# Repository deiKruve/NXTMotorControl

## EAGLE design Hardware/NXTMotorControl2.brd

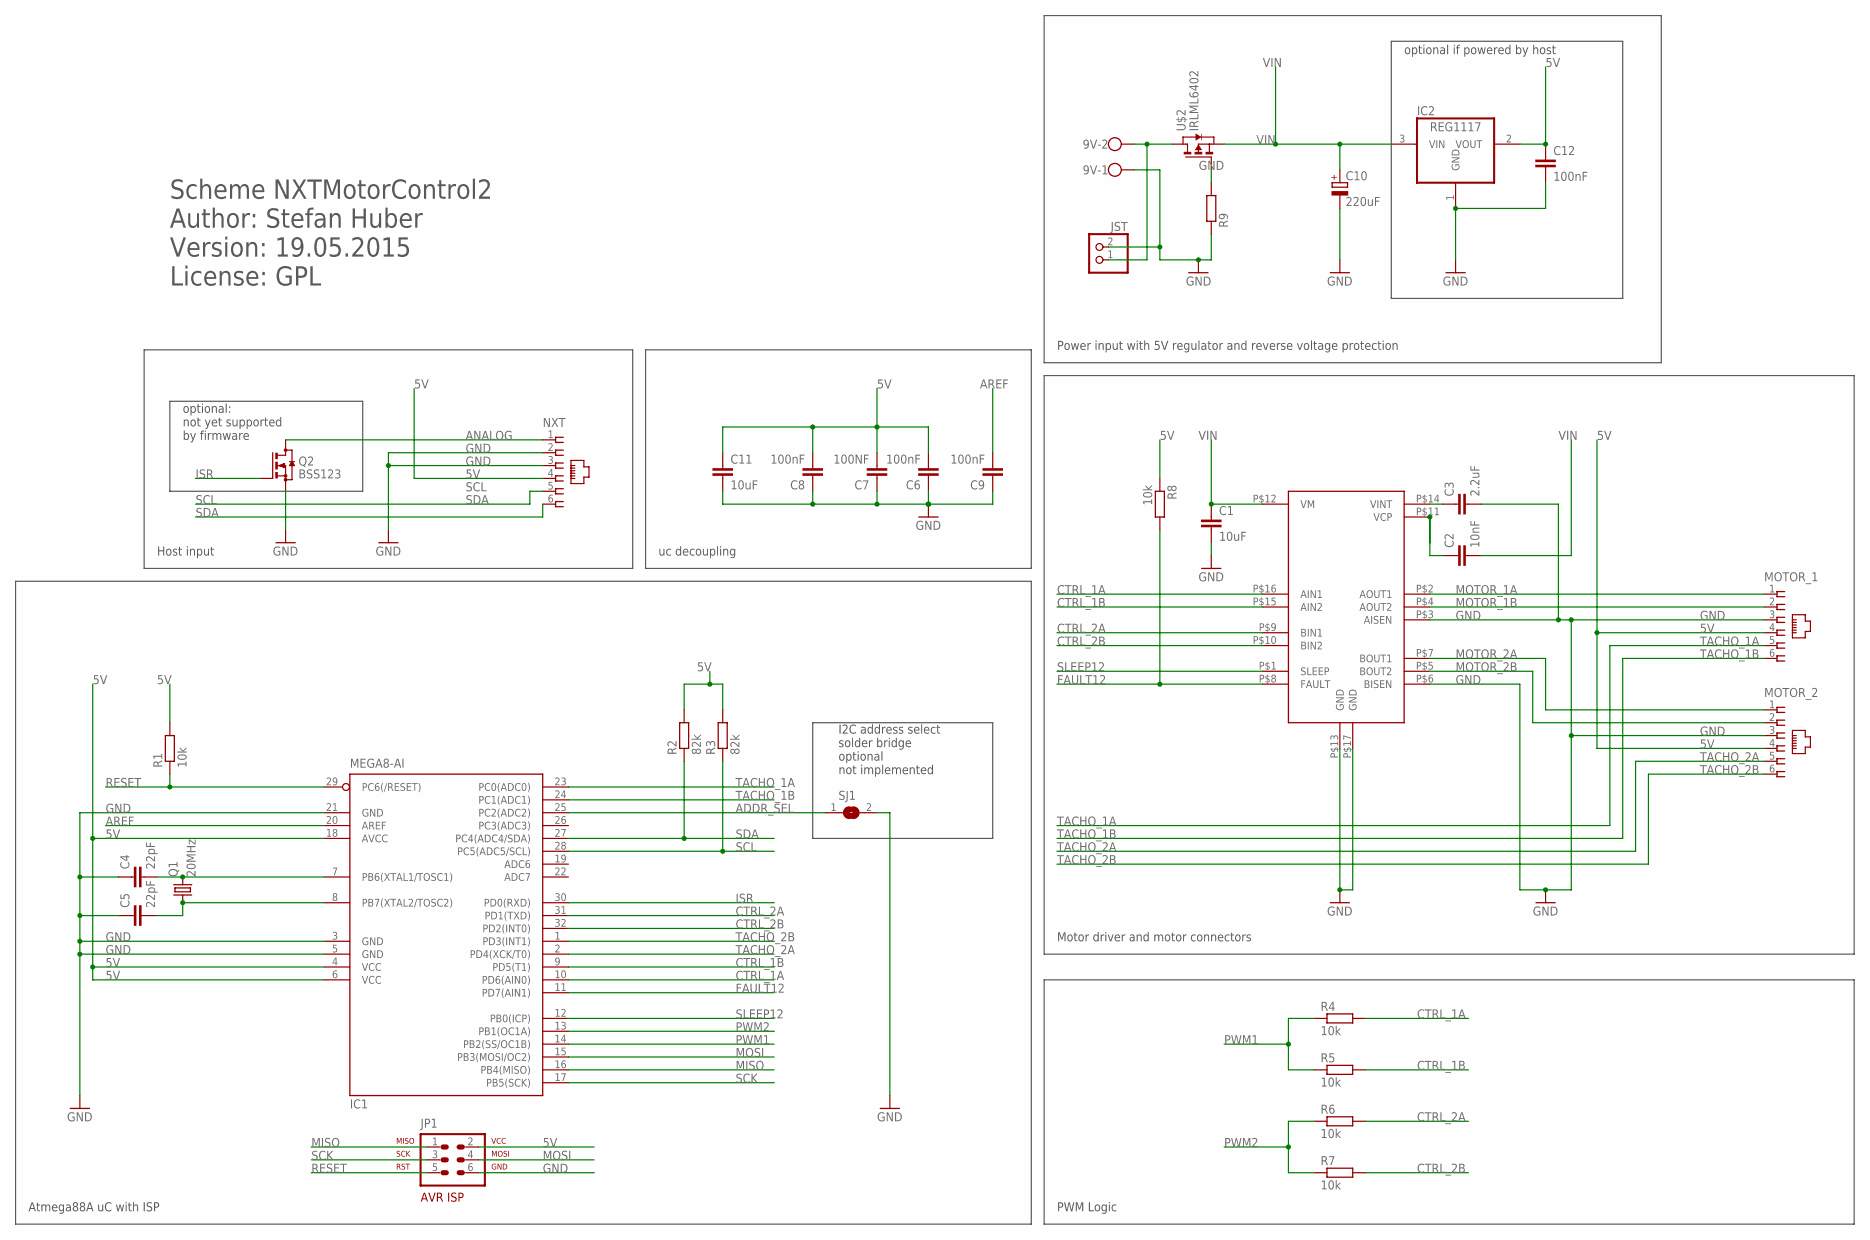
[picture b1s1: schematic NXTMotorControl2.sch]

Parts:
9V: W237-102
C1, C11: 10uF; C0805
C2: 10nF; C0805
C3: 2.2uF; C0805
C4, C5: 22pF; C0805
C6, C8, C9, C12: 100nF; C0805
C7: 100NF; C0805
C10: 220uF; E3,5-8
IC1: MEGA8-AI; TQFP32-08
IC2: REG1117; SOT223
JP1: ISP; AVR-ISP-6
JST: JST_2PIN-THM; JST-PH-2-THM
MOTOR_1, MOTOR_2: NXT
NXT: NXT
Q1: 20MHz; HC49/S
Q2: BSS123; SOT23
R1, R4, R5, R6, R7, R8: 10k; R0805
R2, R3: 82k; R0805
R9: R-EU_R0805; R0805
SJ1: SJ
U$1: DRV8833; HTSSOP16
U$2: IRLML6402; SOT-23

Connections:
5V: C6.2, C7.2, C8.2, C11.1, C12.1, IC1.4 (VCC), IC1.6 (VCC), IC1.18 (AVCC), IC2.2 (VOUT), JP1.2, MOTOR_1.4, MOTOR_2.4, NXT.4, R1.2, R2.2, R3.2, R8.1
ADDR_SEL: IC1.25 (PC2(ADC2)), SJ1.1
ANALOG: NXT.1, Q2.3 (D)
AREF: C9.2, IC1.20 (AREF)
CTRL_1A: IC1.10 (PD6(AIN0)), R4.2, U$1.P$16 (AIN1)
CTRL_1B: IC1.9 (PD5(T1)), R5.2, U$1.P$15 (AIN2)
CTRL_2A: IC1.31 (PD1(TXD)), R6.2, U$1.P$9 (BIN1)
CTRL_2B: IC1.32 (PD2(INT0)), R7.2, U$1.P$10 (BIN2)
FAULT12: IC1.11 (PD7(AIN1)), R8.2, U$1.P$8 (FAULT)
GND: 9V.1, C1.2, C3.2, C4.1, C5.1, C6.1, C7.1, C8.1, C9.1, C10.-, C11.2, C12.2, IC1.3 (GND), IC1.5 (GND), IC1.21 (GND), IC2.1 (GND), JP1.6, JST.2 (1), MOTOR_1.3, MOTOR_2.3, NXT.2, NXT.3, Q2.2 (S), R9.1, SJ1.2, U$1.P$3 (AISEN), U$1.P$6 (BISEN), U$1.P$13 (GND), U$1.P$17 (GND)
ISR: IC1.30 (PD0(RXD)), Q2.1 (G)
MISO: IC1.16 (PB4(MISO)), JP1.1
MOSI: IC1.15 (PB3(MOSI/OC2)), JP1.4
MOTOR_1A: MOTOR_1.1, U$1.P$2 (AOUT1)
MOTOR_1B: MOTOR_1.2, U$1.P$4 (AOUT2)
MOTOR_2A: MOTOR_2.1, U$1.P$7 (BOUT1)
MOTOR_2B: MOTOR_2.2, U$1.P$5 (BOUT2)
unnamed: C4.2, IC1.7 (PB6(XTAL1/TOSC1)), Q1.2
unnamed: C3.1, U$1.P$14 (VINT)
unnamed: C2.1, U$1.P$11 (VCP)
unnamed: C5.2, IC1.8 (PB7(XTAL2/TOSC2)), Q1.1
unnamed: 9V.2, JST.1 (2), U$2.3 (D)
unnamed: R9.2, U$2.1 (G)
PWM1: IC1.14 (PB2(SS/OC1B)), R4.1, R5.1
PWM2: IC1.13 (PB1(OC1A)), R6.1, R7.1
RESET: IC1.29 (PC6(/RESET)), JP1.5, R1.1
SCK: IC1.17 (PB5(SCK)), JP1.3
SCL: IC1.28 (PC5(ADC5/SCL)), NXT.5, R3.1
SDA: IC1.27 (PC4(ADC4/SDA)), NXT.6, R2.1
SLEEP12: IC1.12 (PB0(ICP)), U$1.P$1 (SLEEP)
TACHO_1A: IC1.23 (PC0(ADC0)), MOTOR_1.5
TACHO_1B: IC1.24 (PC1(ADC1)), MOTOR_1.6
TACHO_2A: IC1.2 (PD4(XCK/T0)), MOTOR_2.5
TACHO_2B: IC1.1 (PD3(INT1)), MOTOR_2.6
VIN: C1.1, C2.2, C10.+, IC2.3 (VIN), U$1.P$12 (VM), U$2.2 (S)

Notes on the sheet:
Motor driver and motor connectors
PWM Logic
Power input with 5V regulator and reverse voltage protection
optional if powered by host
uc decoupling
optional: not yet supported by firmware
Host input
Atmega88A uC with ISP
I2C address select solder bridge optional not implemented
Scheme NXTMotorControl2 Author: Stefan Huber Version: 19.05.2015 License: GPL

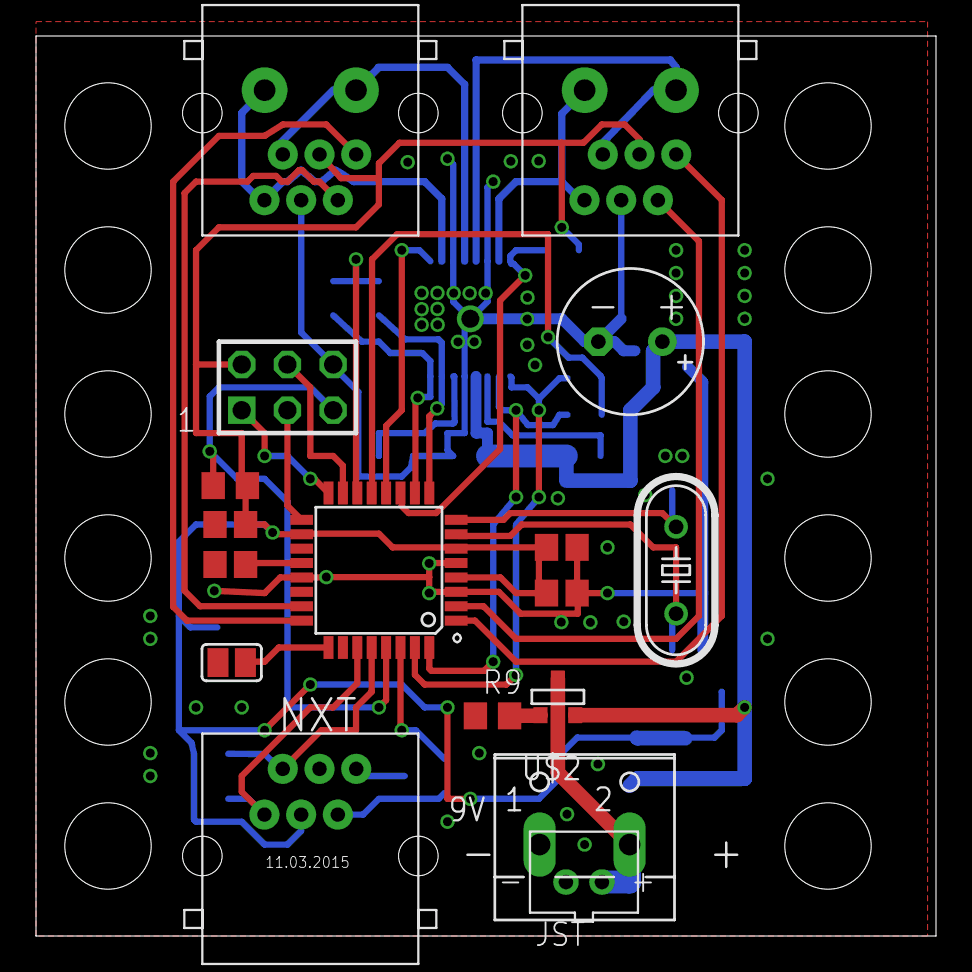
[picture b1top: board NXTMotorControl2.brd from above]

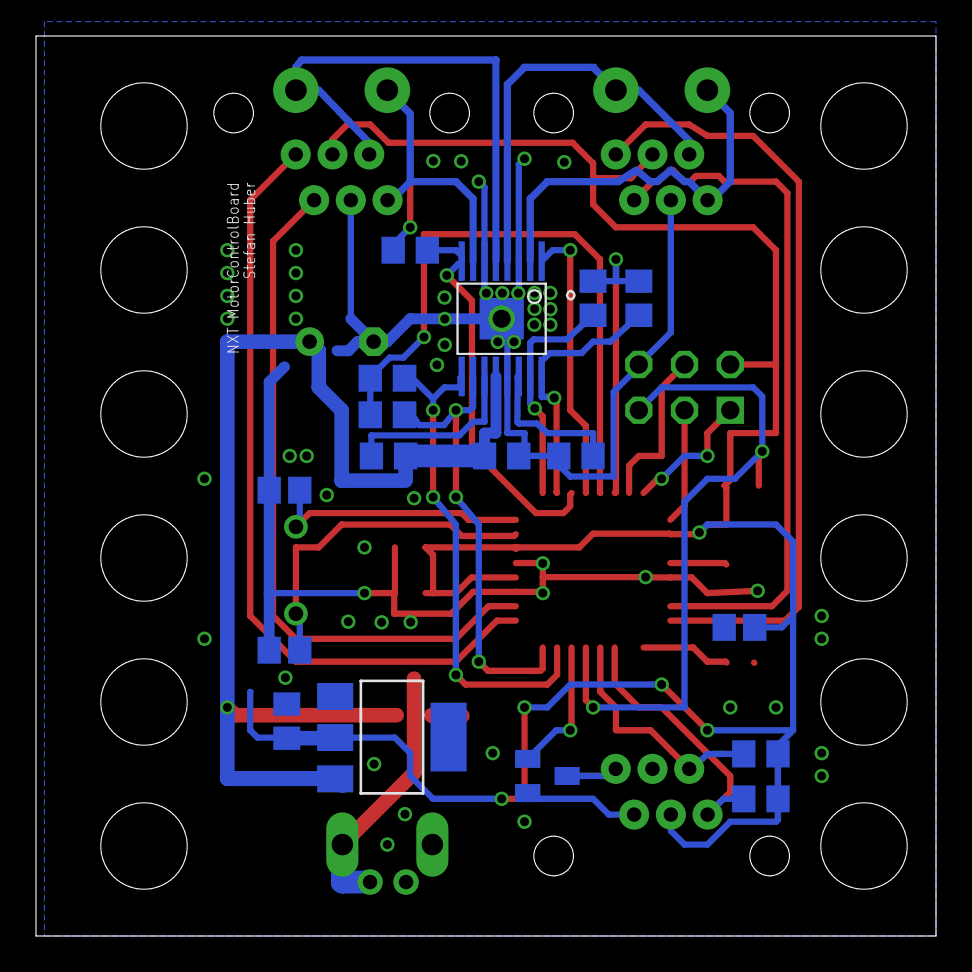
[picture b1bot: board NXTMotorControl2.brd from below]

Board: 2 copper layers, 50.0 x 50.0 mm, 34 parts (17 on the bottom side), 35 nets.

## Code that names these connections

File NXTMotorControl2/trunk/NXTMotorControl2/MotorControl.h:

/*
 * MotorControl.h
 *
 * Created: 12.11.2014 18:02:46
 *	Author: Stefan Huber
 *	page	: http://stefanshacks.blogspot.de/
 *	License	: GNU General Public License
 *
 *	Update	: 16.05.2015
 */ 


#ifndef MOTORCONTROL_H_
#define MOTORCONTROL_H_

#include <inttypes.h>


#define MOTOR_FLOAT		0
#define MOTOR_BREAK		1
#define MOTOR_FORWARD	1
#define MOTOR_BACKWARD	0

void setMotorBreakMode(uint8_t chan, uint8_t mode);		//Sets the motor to either breaking or floating (MOTOR_BREAK or MOTOR_FLOAT)
void setMotorDir(uint8_t chan, uint8_t dir);			//Sets motor direction (either MOTOR_FORWARD or MOTOR_BACKWARD)
uint8_t getMotorDir(uint8_t chan);						//gets current motor direction
void init_MotorGPIO();									//Inits GPIOs for motor control
void init_MotorPWM();									//Inits Timer for motor PWM
void setMotorPWM(uint8_t chan,  uint8_t  pwm);			//Sets motor PWM value
uint8_t getMotorPWM(uint8_t chan);						//Gets the current motor pwm value

//GPIO Assignment
#define CTRL_DDR	DDRD
#define CTRL_PORT	PORTD
#define CTRL_2A		(1<<1)
#define CTRL_2B		(1<<2)
#define CTRL_1B		(1<<5)
#define CTRL_1A		(1<<6)

#define PWM_DDR		DDRB
#define PWM_PORT	PORTB
#define PWM1		(1<<1)
#define PWM2		(1<<2)

#define FAULT_DDR	DDRD
#define FAULT_PIN	PIND
#define FAULT12		(1<<7)

#define SLEEP_DDR	DDRB
#define SLEEP_PORT	PORTB
#define SLEEP_PIN	PINB
#define SLEEP12		(1<<0)

#define SPEED1		OCR1B	//OC1B
#define SPEED2		OCR1A	//OC1A



#endif /* MOTORCONTROL_H_ */

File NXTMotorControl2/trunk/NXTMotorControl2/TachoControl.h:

/*
 * TachoControl.h
 *
 * Created: 12.11.2014 18:07:41
 *	Author: Stefan Huber
 *	page	: http://stefanshacks.blogspot.de/
 *	License	: GNU General Public License
 *
 *	Update	: 16.05.2015
 */ 

#ifndef TACHOCONTROL_H_
#define TACHOCONTROL_H_

#include <inttypes.h>

//Configuration of Tacho Readout frequency


#define TACHO_TICKS_PER_TURN	720UL


//GPIO Assignment
#define TACHO1_DDR		DDRC
#define TACHO1_PORT		PORTC
#define TACHO1_PIN		PINC
#define TACHO1B			(1<<PC0)
#define TACHO1A			(1<<PC1)
#define TACHO1_PHASEB	(TACHO1_PIN & TACHO1A)
#define TACHO1_PHASEA	(TACHO1_PIN & TACHO1B)
#define TACHO1_ISR_MSK	((1<<PCINT9) | (1<<PCINT8))

#define TACHO2_DDR		DDRD
#define TACHO2_PORT		PORTD
#define TACHO2_PIN		PIND
#define TACHO2A			(1<<PD4)
#define TACHO2B			(1<<PD3)
#define TACHO2_PHASEA	(TACHO2_PIN & TACHO2A)
#define TACHO2_PHASEB	(TACHO2_PIN & TACHO2B)
#define TACHO2_ISR_MSK	((1<<PCINT11) | (1<<PCINT12))

void init_tacho();
int8_t encode_read(uint8_t chan);




#endif /* TACHOCONTROL_H_ */

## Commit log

2015-05-17 :boom::camel: Added .gitattributes
2015-05-17 First Commit
    First Commit of both project files
2015-05-20 Added Hardware
